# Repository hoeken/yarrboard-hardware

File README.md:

# Yarrboard Hardware

This repo has Kicad symbols, footprints, and models used in the Yarrboard project.

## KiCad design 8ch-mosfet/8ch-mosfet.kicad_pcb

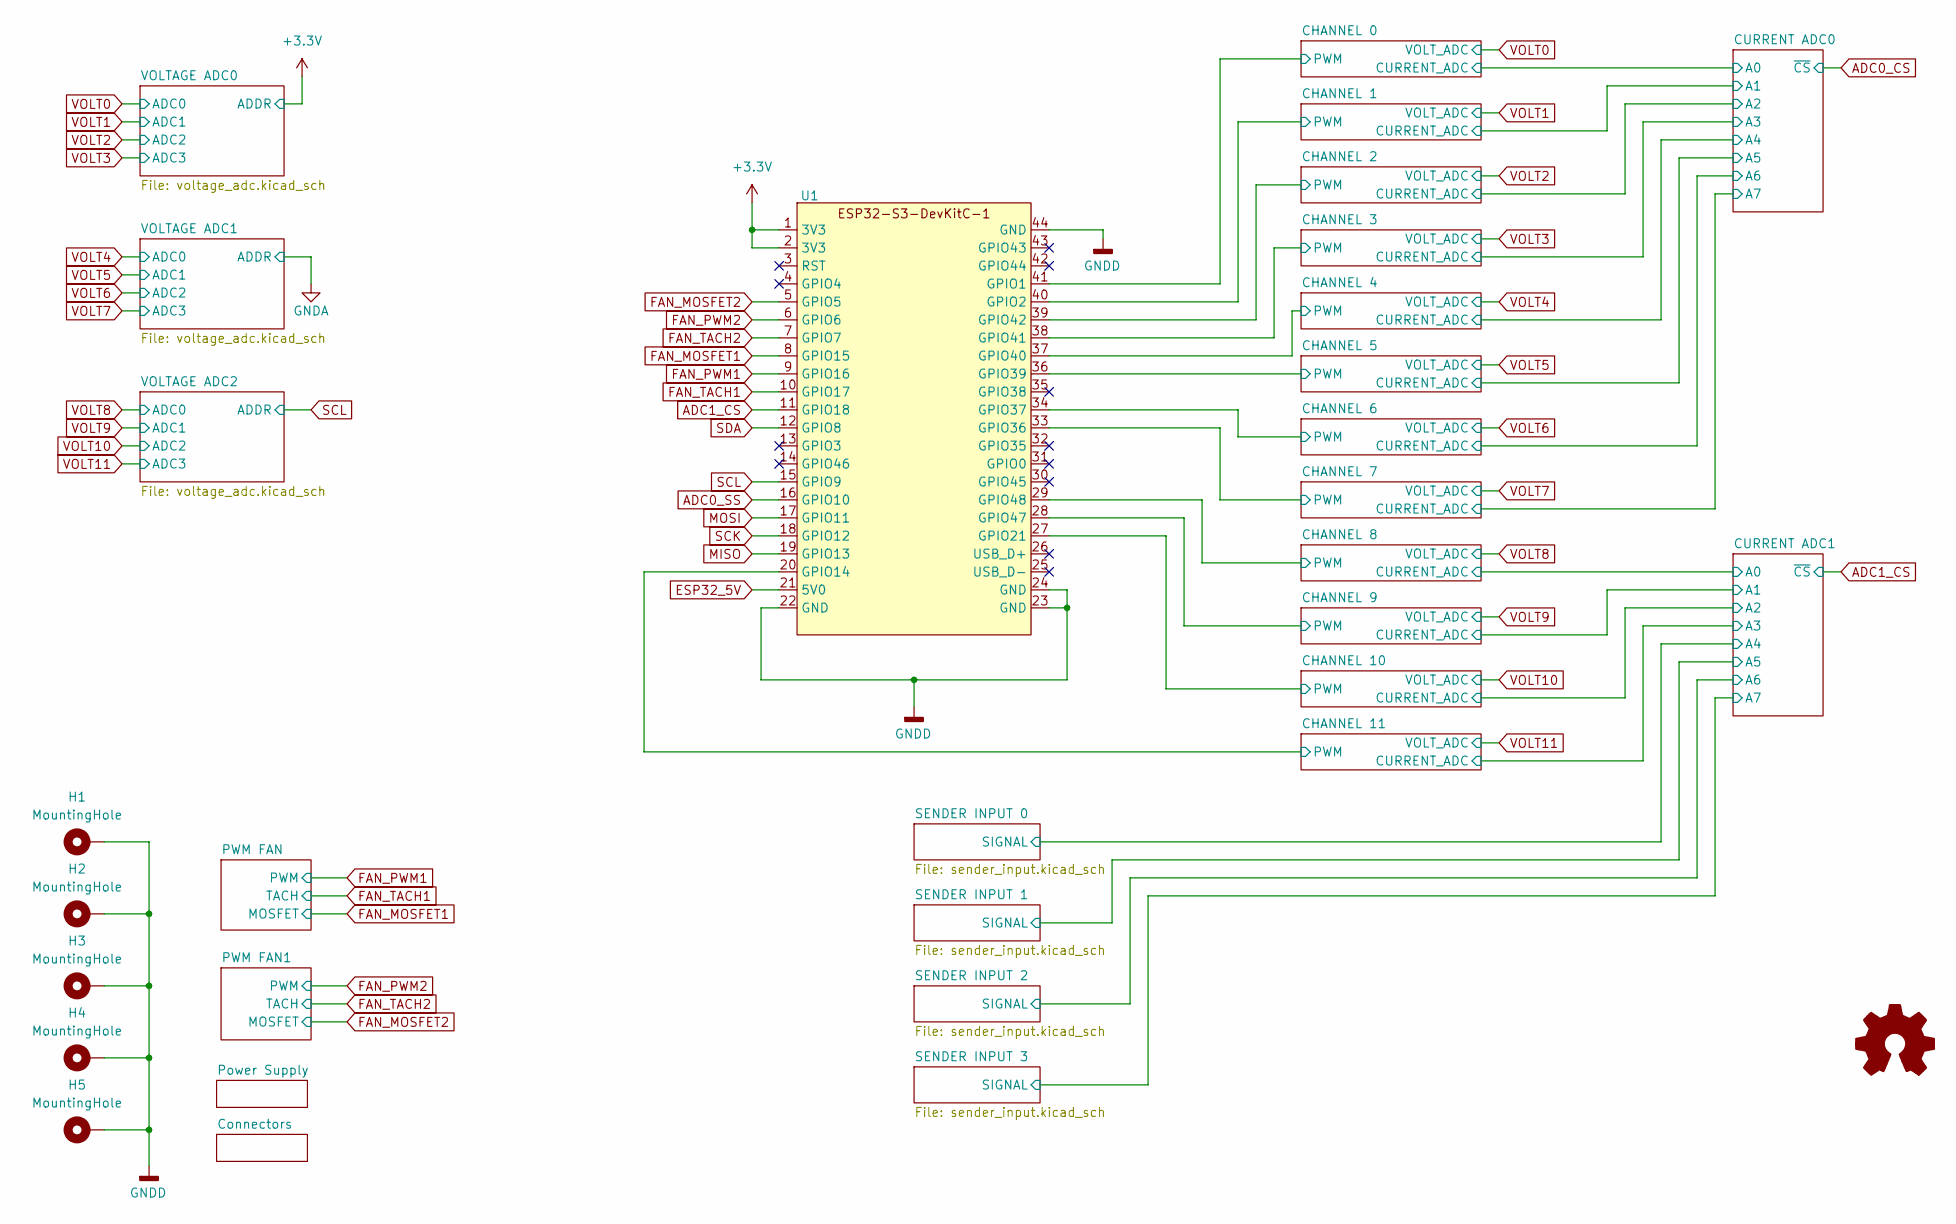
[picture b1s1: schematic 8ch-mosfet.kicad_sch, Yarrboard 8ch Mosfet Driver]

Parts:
H1, H2, H3, H4, H5: MountingHole; MountingHole_3.2mm_M3_DIN965_Pad
U1: Waveshare-ESP32-S3-dev-kit

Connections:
+3.3V: U1.1 (3V3), U1.2 (3V3); also elsewhere on the board
/CHANNEL 0/PWM: U1.41 (GPIO1); also elsewhere on the board
/CHANNEL 1/PWM: U1.40 (GPIO2); also elsewhere on the board
/CHANNEL 2/PWM: U1.39 (GPIO42); also elsewhere on the board
/CHANNEL 3/PWM: U1.38 (GPIO41); also elsewhere on the board
/CHANNEL 4/PWM: U1.37 (GPIO40); also elsewhere on the board
/CHANNEL 5/PWM: U1.36 (GPIO39); also elsewhere on the board
/CHANNEL 6/PWM: U1.34 (GPIO37); also elsewhere on the board
/CHANNEL 7/PWM: U1.33 (GPIO36); also elsewhere on the board
/CHANNEL 8/PWM: U1.29 (GPIO48); also elsewhere on the board
/CHANNEL 9/PWM: U1.28 (GPIO47); also elsewhere on the board
/CHANNEL 10/PWM: U1.27 (GPIO21); also elsewhere on the board
/CHANNEL 11/PWM: U1.20 (GPIO14); also elsewhere on the board
ADC0_SS: U1.16 (GPIO10)
ADC1_CS: U1.11 (GPIO18); also elsewhere on the board
ESP32_5V: U1.21 (5V0); also elsewhere on the board
FAN_MOSFET1: U1.8 (GPIO15); also elsewhere on the board
FAN_MOSFET2: U1.5 (GPIO5); also elsewhere on the board
FAN_PWM1: U1.9 (GPIO16); also elsewhere on the board
FAN_PWM2: U1.6 (GPIO6); also elsewhere on the board
FAN_TACH1: U1.10 (GPIO17); also elsewhere on the board
FAN_TACH2: U1.7 (GPIO7); also elsewhere on the board
GNDD: H1.1, H2.1, H3.1, H4.1, H5.1, U1.22 (GND), U1.23 (GND), U1.24 (GND), U1.44 (GND); also elsewhere on the board
MISO: U1.19 (GPIO13); also elsewhere on the board
MOSI: U1.17 (GPIO11); also elsewhere on the board
SCK: U1.18 (GPIO12); also elsewhere on the board
SCL: U1.15 (GPIO9); also elsewhere on the board
SDA: U1.12 (GPIO8); also elsewhere on the board

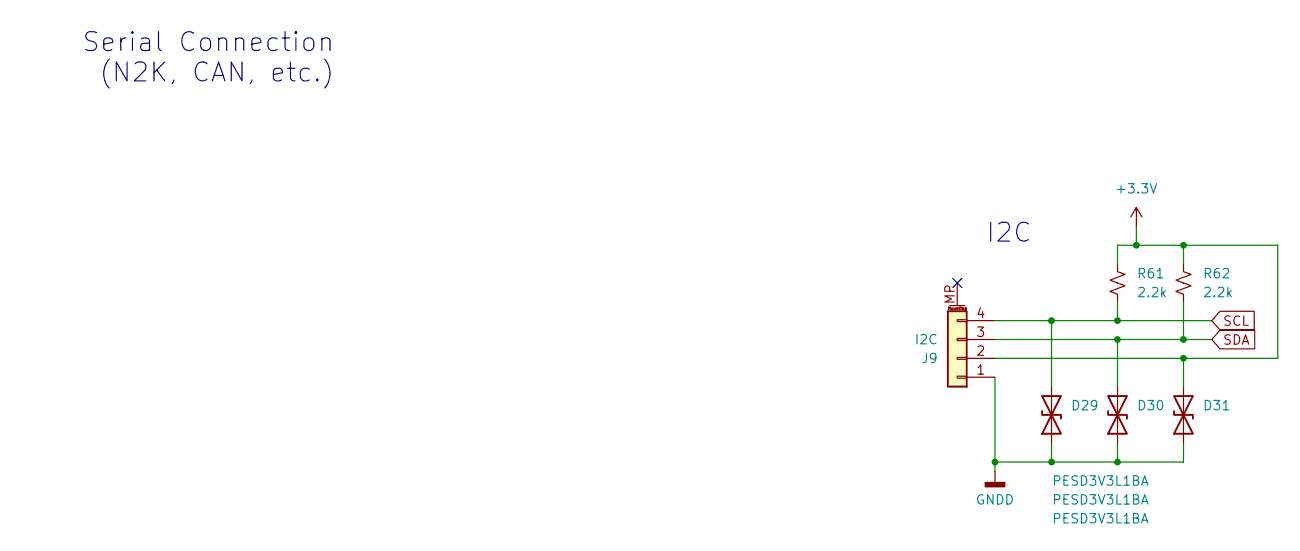
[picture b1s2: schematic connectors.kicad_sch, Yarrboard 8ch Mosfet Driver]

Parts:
D29, D30, D31: PESD3V3L1BA; D_SOD-323_HandSoldering; LCSC C316020
J9: I2C; JST_SH_SM04B-SRSS-TB_1x04-1MP_P1.00mm_Horizontal; LCSC C160404
R61, R62: 2.2k; R_0805_2012Metric_Pad1.20x1.40mm_HandSolder

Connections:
+3.3V: D31.2 (A2), J9.2, R61.2, R62.2; also elsewhere on the board
GNDD: D29.1 (A1), D30.1 (A1), D31.1 (A1), J9.1; also elsewhere on the board
SCL: D29.2 (A2), J9.4, R61.1; also elsewhere on the board
SDA: D30.2 (A2), J9.3, R62.1; also elsewhere on the board

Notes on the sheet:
Serial Connection (N2K, CAN, etc.)
I2C

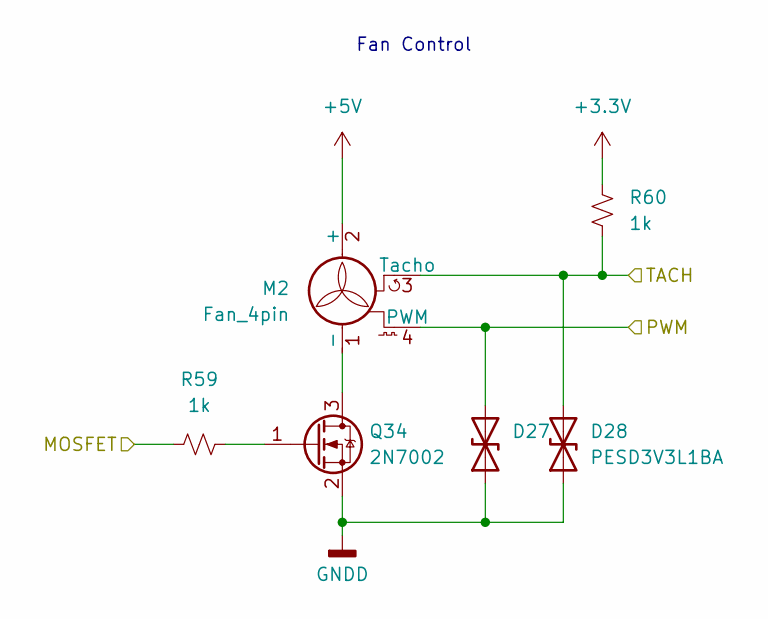
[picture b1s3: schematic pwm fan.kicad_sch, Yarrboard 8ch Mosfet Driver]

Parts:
D27, D28: PESD3V3L1BA; D_SOD-323_HandSoldering; LCSC C316020
M2: Fan_4pin; Molex 0470531000; Mouser 538-47053-1000
Q34: 2N7002; SOT-23
R59, R60: 1k; R_0805_2012Metric_Pad1.20x1.40mm_HandSolder; LCSC C95781

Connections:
+3.3V: R60.2; also elsewhere on the board
+5V: M2.2 (+); also elsewhere on the board
FAN_MOSFET2: R59.2; also elsewhere on the board
FAN_PWM2: D27.2 (A2), M2.4 (PWM); also elsewhere on the board
FAN_TACH2: D28.2 (A2), M2.3 (Tacho), R60.1; also elsewhere on the board
GNDD: D27.1 (A1), D28.1 (A1), Q34.2 (S); also elsewhere on the board
unnamed: M2.1 (-), Q34.3 (D)
unnamed: Q34.1 (G), R59.1

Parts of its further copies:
D25, D26: PESD3V3L1BA; D_SOD-323_HandSoldering; LCSC C316020
M1: Fan_4pin; Molex 0470531000; Mouser 538-47053-1000
Q33: 2N7002; SOT-23
R57, R58: 1k; R_0805_2012Metric_Pad1.20x1.40mm_HandSolder; LCSC C95781

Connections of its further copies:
+3.3V: R58.2; also elsewhere on the board
+5V: M1.2 (+); also elsewhere on the board
FAN_MOSFET1: R57.2; also elsewhere on the board
FAN_PWM1: D25.2 (A2), M1.4 (PWM); also elsewhere on the board
FAN_TACH1: D26.2 (A2), M1.3 (Tacho), R58.1; also elsewhere on the board
GNDD: D25.1 (A1), D26.1 (A1), Q33.2 (S); also elsewhere on the board
unnamed: M1.1 (-), Q33.3 (D)
unnamed: Q33.1 (G), R57.1

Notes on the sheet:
Fan Control

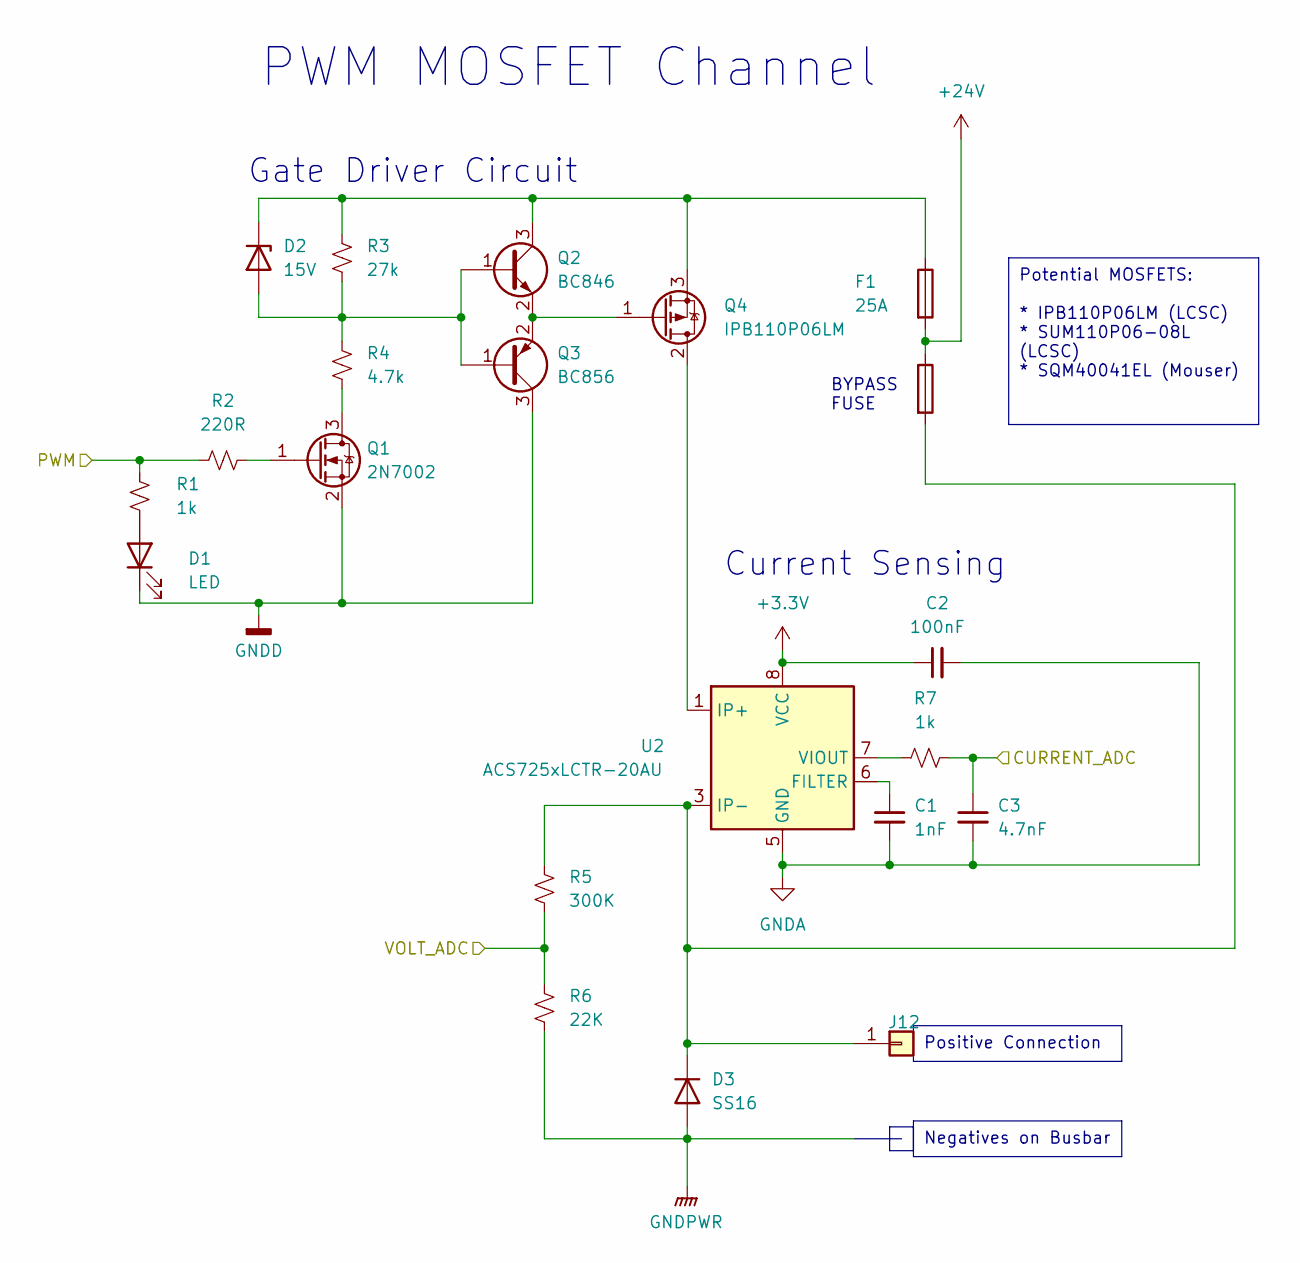
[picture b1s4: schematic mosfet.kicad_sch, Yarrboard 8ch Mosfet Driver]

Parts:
C1: 1nF; C_0805_2012Metric_Pad1.18x1.45mm_HandSolder; Mouser C0805C102J1HACTU
C2: 100nF; C_0805_2012Metric_Pad1.18x1.45mm_HandSolder; Mouser 08053C104KAT4A
C3: 4.7nF; C_0805_2012Metric_Pad1.18x1.45mm_HandSolder; Mouser C0805C472K5RAC
D1: LED; LED_0805_2012Metric_Pad1.15x1.40mm_HandSolder; Mouser 150080RS75000
D2: 15V; D_SOD-323_HandSoldering; Mouser 771-BZX384-C15115
D3: SS16; D_SMA; Mouser 625-SS16-E3
F1: 25A; ATC Bypass Fuse; Mouser 534-3522-3
J12: Conn_01x01; T44001
Q1: 2N7002; SOT-23
Q2: BC846; SOT-23
Q3: BC856; SOT-23
Q4: IPB110P06LM; TO-263-2
R1, R7: 1k; R_0805_2012Metric_Pad1.20x1.40mm_HandSolder; LCSC C95781
R2: 220R; R_0805_2012Metric_Pad1.20x1.40mm_HandSolder; LCSC C114519
R3: 27k; R_0805_2012Metric_Pad1.20x1.40mm_HandSolder
R4: 4.7k; R_0805_2012Metric_Pad1.20x1.40mm_HandSolder
R5: 300K; R_0805_2012Metric_Pad1.20x1.40mm_HandSolder
R6: 22K; R_0805_2012Metric_Pad1.20x1.40mm_HandSolder; LCSC C865312
U2: ACS725xLCTR-20AU; ACS7XX; Mouser 250-725LLCTR20AUT

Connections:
+3.3V: C2.1, U2.8 (VCC); also elsewhere on the board
+24V: F1.2; also elsewhere on the board
/CHANNEL 0/CURRENT_ADC: C3.1, R7.1; also elsewhere on the board
/CHANNEL 0/PWM: R1.2, R2.1; also elsewhere on the board
GNDA: C1.2, C2.2, C3.2, U2.5 (GND); also elsewhere on the board
GNDD: D1.1 (K), Q1.2 (S), Q3.3 (C); also elsewhere on the board
GNDPWR: D3.2 (A), R6.1; also elsewhere on the board
unnamed: D1.2 (A), R1.1
unnamed: D2.2 (A), Q2.1 (B), Q3.1 (B), R3.1, R4.2
unnamed: D2.1 (K), F1.1, Q2.3 (C), Q4.3 (S), R3.2
unnamed: Q1.3 (D), R4.1
unnamed: Q1.1 (G), R2.2
unnamed: Q2.2 (E), Q3.2 (E), Q4.1 (G)
unnamed: Q4.2 (D), U2.1 (IP+), U2.2 (IP+)
unnamed: C1.1, U2.6 (FILTER)
unnamed: R7.2, U2.7 (VIOUT)
VOLT0: R5.1, R6.2; also elsewhere on the board

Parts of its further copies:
C4, C7, C10, C13, C16, C19, C22, C37, C40, C43, C46: 1nF; C_0805_2012Metric_Pad1.18x1.45mm_HandSolder; Mouser C0805C102J1HACTU
C5, C8, C11, C14, C17, C20, C23, C38, C41, C44, C47: 100nF; C_0805_2012Metric_Pad1.18x1.45mm_HandSolder; Mouser 08053C104KAT4A
C6, C9, C12, C15, C18, C21, C24, C39, C42, C45, C48: 4.7nF; C_0805_2012Metric_Pad1.18x1.45mm_HandSolder; Mouser C0805C472K5RAC
D4, D7, D10, D13, D16, D19, D22, D37, D40, D43, D46: LED; LED_0805_2012Metric_Pad1.15x1.40mm_HandSolder; Mouser 150080RS75000
D5, D8, D11, D14, D17, D20, D23, D38, D41, D44, D47: 15V; D_SOD-323_HandSoldering; Mouser 771-BZX384-C15115
D6, D9, D12, D15, D18, D21, D24, D39, D42, D45, D48: SS16; D_SMA; Mouser 625-SS16-E3
F2, F3, F4, F5, F6, F7, F8, F11, F12, F13, F14: 25A; ATC Bypass Fuse; Mouser 534-3522-3
J1, J2, J3, J4, J5, J6, J7, J8, J13, J14, J15: Conn_01x01; T44001
Q5, Q9, Q13, Q17, Q21, Q25, Q29, Q35, Q39, Q43, Q47: 2N7002; SOT-23
Q6, Q10, Q14, Q18, Q22, Q26, Q30, Q36, Q40, Q44, Q48: BC846; SOT-23
Q7, Q11, Q15, Q19, Q23, Q27, Q31, Q37, Q41, Q45, Q49: BC856; SOT-23
Q8, Q12, Q16, Q20, Q24, Q28, Q32, Q38, Q42, Q46, Q50: IPB110P06LM; TO-263-2
R8, R14, R15, R21, R22, R28, R29, R35, R36, R42, R43, R49, R50, R56, R69, R75, R76, R82, R83, R89, R90, R96: 1k; R_0805_2012Metric_Pad1.20x1.40mm_HandSolder; LCSC C95781
R9, R16, R23, R30, R37, R44, R51, R70, R77, R84, R91: 220R; R_0805_2012Metric_Pad1.20x1.40mm_HandSolder; LCSC C114519
R10, R17, R24, R31, R38, R45, R52, R71, R78, R85, R92: 27k; R_0805_2012Metric_Pad1.20x1.40mm_HandSolder
R11, R18, R25, R32, R39, R46, R53, R72, R79, R86, R93: 4.7k; R_0805_2012Metric_Pad1.20x1.40mm_HandSolder
R12, R19, R26, R33, R40, R47, R54, R73, R80, R87, R94: 300K; R_0805_2012Metric_Pad1.20x1.40mm_HandSolder
R13, R20, R27, R34, R41, R48, R55, R74, R81, R88, R95: 22K; R_0805_2012Metric_Pad1.20x1.40mm_HandSolder; LCSC C865312
U3, U4, U5, U6, U7, U8, U9, U15, U16, U17, U18: ACS725xLCTR-20AU; ACS7XX; Mouser 250-725LLCTR20AUT

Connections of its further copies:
+3.3V: C5.1, C8.1, C11.1, C14.1, C17.1, C20.1, C23.1, C38.1, C41.1, C44.1, C47.1, U3.8 (VCC), U4.8 (VCC), U5.8 (VCC), U6.8 (VCC), U7.8 (VCC), U8.8 (VCC), U9.8 (VCC), U15.8 (VCC), U16.8 (VCC), U17.8 (VCC), U18.8 (VCC); also elsewhere on the board
+24V: F2.2, F3.2, F4.2, F5.2, F6.2, F7.2, F8.2, F11.2, F12.2, F13.2, F14.2; also elsewhere on the board
/CHANNEL 1/CURRENT_ADC: C6.1, R14.1; also elsewhere on the board
/CHANNEL 1/PWM: R8.2, R9.1; also elsewhere on the board
/CHANNEL 2/CURRENT_ADC: C9.1, R21.1; also elsewhere on the board
/CHANNEL 2/PWM: R15.2, R16.1; also elsewhere on the board
/CHANNEL 3/CURRENT_ADC: C12.1, R28.1; also elsewhere on the board
/CHANNEL 3/PWM: R22.2, R23.1; also elsewhere on the board
/CHANNEL 4/CURRENT_ADC: C15.1, R35.1; also elsewhere on the board
/CHANNEL 4/PWM: R29.2, R30.1; also elsewhere on the board
/CHANNEL 5/CURRENT_ADC: C18.1, R42.1; also elsewhere on the board
/CHANNEL 5/PWM: R36.2, R37.1; also elsewhere on the board
/CHANNEL 6/CURRENT_ADC: C21.1, R49.1; also elsewhere on the board
/CHANNEL 6/PWM: R43.2, R44.1; also elsewhere on the board
/CHANNEL 7/CURRENT_ADC: C24.1, R56.1; also elsewhere on the board
/CHANNEL 7/PWM: R50.2, R51.1; also elsewhere on the board
/CHANNEL 8/CURRENT_ADC: C39.1, R75.1; also elsewhere on the board
/CHANNEL 8/PWM: R69.2, R70.1; also elsewhere on the board
/CHANNEL 9/CURRENT_ADC: C42.1, R82.1; also elsewhere on the board
/CHANNEL 9/PWM: R76.2, R77.1; also elsewhere on the board
/CHANNEL 10/CURRENT_ADC: C45.1, R89.1; also elsewhere on the board
/CHANNEL 10/PWM: R83.2, R84.1; also elsewhere on the board
/CHANNEL 11/CURRENT_ADC: C48.1, R96.1; also elsewhere on the board
/CHANNEL 11/PWM: R90.2, R91.1; also elsewhere on the board
GNDA: C4.2, C5.2, C6.2, C7.2, C8.2, C9.2, C10.2, C11.2, C12.2, C13.2, C14.2, C15.2, C16.2, C17.2, C18.2, C19.2, C20.2, C21.2, C22.2, C23.2, C24.2, C37.2, C38.2, C39.2, C40.2, C41.2, C42.2, C43.2, C44.2, C45.2, C46.2, C47.2, C48.2, U3.5 (GND), U4.5 (GND), U5.5 (GND), U6.5 (GND), U7.5 (GND), U8.5 (GND), U9.5 (GND), U15.5 (GND), U16.5 (GND), U17.5 (GND), U18.5 (GND); also elsewhere on the board
GNDD: D4.1 (K), D7.1 (K), D10.1 (K), D13.1 (K), D16.1 (K), D19.1 (K), D22.1 (K), D37.1 (K), D40.1 (K), D43.1 (K), D46.1 (K), Q5.2 (S), Q7.3 (C), Q9.2 (S), Q11.3 (C), Q13.2 (S), Q15.3 (C), Q17.2 (S), Q19.3 (C), Q21.2 (S), Q23.3 (C), Q25.2 (S), Q27.3 (C), Q29.2 (S), Q31.3 (C), Q35.2 (S), Q37.3 (C), Q39.2 (S), Q41.3 (C), Q43.2 (S), Q45.3 (C), Q47.2 (S), Q49.3 (C); also elsewhere on the board
GNDPWR: D6.2 (A), D9.2 (A), D12.2 (A), D15.2 (A), D18.2 (A), D21.2 (A), D24.2 (A), D39.2 (A), D42.2 (A), D45.2 (A), D48.2 (A), R13.1, R20.1, R27.1, R34.1, R41.1, R48.1, R55.1, R74.1, R81.1, R88.1, R95.1; also elsewhere on the board
unnamed: D4.2 (A), R8.1
unnamed: D5.2 (A), Q6.1 (B), Q7.1 (B), R10.1, R11.2
unnamed: D5.1 (K), F2.1, Q6.3 (C), Q8.3 (S), R10.2
unnamed: D6.1 (K), F2.3, J2.1, R12.2, U3.3 (IP-), U3.4 (IP-)
unnamed: D7.2 (A), R15.1
unnamed: D8.2 (A), Q10.1 (B), Q11.1 (B), R17.1, R18.2
unnamed: D8.1 (K), F3.1, Q10.3 (C), Q12.3 (S), R17.2
unnamed: D9.1 (K), F3.3, J3.1, R19.2, U4.3 (IP-), U4.4 (IP-)
unnamed: D10.2 (A), R22.1
unnamed: D11.2 (A), Q14.1 (B), Q15.1 (B), R24.1, R25.2
unnamed: D11.1 (K), F4.1, Q14.3 (C), Q16.3 (S), R24.2
unnamed: D12.1 (K), F4.3, J4.1, R26.2, U5.3 (IP-), U5.4 (IP-)
unnamed: D13.2 (A), R29.1
unnamed: D14.2 (A), Q18.1 (B), Q19.1 (B), R31.1, R32.2
unnamed: D14.1 (K), F5.1, Q18.3 (C), Q20.3 (S), R31.2
unnamed: D15.1 (K), F5.3, J5.1, R33.2, U6.3 (IP-), U6.4 (IP-)
unnamed: D16.2 (A), R36.1
unnamed: D17.2 (A), Q22.1 (B), Q23.1 (B), R38.1, R39.2
unnamed: D17.1 (K), F6.1, Q22.3 (C), Q24.3 (S), R38.2
unnamed: D18.1 (K), F6.3, J6.1, R40.2, U7.3 (IP-), U7.4 (IP-)
unnamed: D19.2 (A), R43.1
unnamed: D20.2 (A), Q26.1 (B), Q27.1 (B), R45.1, R46.2
unnamed: D20.1 (K), F7.1, Q26.3 (C), Q28.3 (S), R45.2
unnamed: D21.1 (K), F7.3, J7.1, R47.2, U8.3 (IP-), U8.4 (IP-)
unnamed: D22.2 (A), R50.1
unnamed: D23.2 (A), Q30.1 (B), Q31.1 (B), R52.1, R53.2
unnamed: D23.1 (K), F8.1, Q30.3 (C), Q32.3 (S), R52.2
unnamed: D24.1 (K), F8.3, J8.1, R54.2, U9.3 (IP-), U9.4 (IP-)
unnamed: D37.2 (A), R69.1
unnamed: D38.2 (A), Q36.1 (B), Q37.1 (B), R71.1, R72.2
unnamed: D38.1 (K), F11.1, Q36.3 (C), Q38.3 (S), R71.2
unnamed: D40.2 (A), R76.1
unnamed: D41.2 (A), Q40.1 (B), Q41.1 (B), R78.1, R79.2
unnamed: D41.1 (K), F12.1, Q40.3 (C), Q42.3 (S), R78.2
unnamed: D42.1 (K), F12.3, J13.1, R80.2, U16.3 (IP-), U16.4 (IP-)
unnamed: D43.2 (A), R83.1
unnamed: D44.2 (A), Q44.1 (B), Q45.1 (B), R85.1, R86.2
unnamed: D44.1 (K), F13.1, Q44.3 (C), Q46.3 (S), R85.2
unnamed: D45.1 (K), F13.3, J14.1, R87.2, U17.3 (IP-), U17.4 (IP-)
unnamed: D46.2 (A), R90.1
unnamed: D47.2 (A), Q48.1 (B), Q49.1 (B), R92.1, R93.2
unnamed: D47.1 (K), F14.1, Q48.3 (C), Q50.3 (S), R92.2
unnamed: D48.1 (K), F14.3, J15.1, R94.2, U18.3 (IP-), U18.4 (IP-)
unnamed: Q5.3 (D), R11.1
unnamed: Q5.1 (G), R9.2
unnamed: Q6.2 (E), Q7.2 (E), Q8.1 (G)
unnamed: Q8.2 (D), U3.1 (IP+), U3.2 (IP+)
unnamed: Q9.3 (D), R18.1
unnamed: Q9.1 (G), R16.2
unnamed: Q10.2 (E), Q11.2 (E), Q12.1 (G)
unnamed: Q12.2 (D), U4.1 (IP+), U4.2 (IP+)
unnamed: Q13.3 (D), R25.1
unnamed: Q13.1 (G), R23.2
unnamed: Q14.2 (E), Q15.2 (E), Q16.1 (G)
unnamed: Q16.2 (D), U5.1 (IP+), U5.2 (IP+)
unnamed: Q17.3 (D), R32.1
unnamed: Q17.1 (G), R30.2
unnamed: Q18.2 (E), Q19.2 (E), Q20.1 (G)
unnamed: Q20.2 (D), U6.1 (IP+), U6.2 (IP+)
unnamed: Q21.3 (D), R39.1
unnamed: Q21.1 (G), R37.2
unnamed: Q22.2 (E), Q23.2 (E), Q24.1 (G)
unnamed: Q24.2 (D), U7.1 (IP+), U7.2 (IP+)
unnamed: Q25.3 (D), R46.1
unnamed: Q25.1 (G), R44.2
unnamed: Q26.2 (E), Q27.2 (E), Q28.1 (G)
unnamed: Q28.2 (D), U8.1 (IP+), U8.2 (IP+)
unnamed: Q29.3 (D), R53.1
unnamed: Q29.1 (G), R51.2
unnamed: Q30.2 (E), Q31.2 (E), Q32.1 (G)
unnamed: Q32.2 (D), U9.1 (IP+), U9.2 (IP+)
unnamed: Q35.3 (D), R72.1
unnamed: Q35.1 (G), R70.2
unnamed: Q36.2 (E), Q37.2 (E), Q38.1 (G)
unnamed: Q38.2 (D), U15.1 (IP+), U15.2 (IP+)
unnamed: Q39.3 (D), R79.1
unnamed: Q39.1 (G), R77.2
unnamed: Q40.2 (E), Q41.2 (E), Q42.1 (G)
unnamed: Q42.2 (D), U16.1 (IP+), U16.2 (IP+)
unnamed: Q43.3 (D), R86.1
unnamed: Q43.1 (G), R84.2
unnamed: Q44.2 (E), Q45.2 (E), Q46.1 (G)
unnamed: Q46.2 (D), U17.1 (IP+), U17.2 (IP+)
unnamed: Q47.3 (D), R93.1
unnamed: Q47.1 (G), R91.2
unnamed: Q48.2 (E), Q49.2 (E), Q50.1 (G)
unnamed: Q50.2 (D), U18.1 (IP+), U18.2 (IP+)
unnamed: C4.1, U3.6 (FILTER)
unnamed: R14.2, U3.7 (VIOUT)
unnamed: C7.1, U4.6 (FILTER)
unnamed: R21.2, U4.7 (VIOUT)
unnamed: C10.1, U5.6 (FILTER)
unnamed: R28.2, U5.7 (VIOUT)
unnamed: C13.1, U6.6 (FILTER)
unnamed: R35.2, U6.7 (VIOUT)
unnamed: C16.1, U7.6 (FILTER)
unnamed: R42.2, U7.7 (VIOUT)
unnamed: C19.1, U8.6 (FILTER)
unnamed: R49.2, U8.7 (VIOUT)
unnamed: C22.1, U9.6 (FILTER)
unnamed: R56.2, U9.7 (VIOUT)
unnamed: C37.1, U15.6 (FILTER)
unnamed: R75.2, U15.7 (VIOUT)
unnamed: C40.1, U16.6 (FILTER)
unnamed: R82.2, U16.7 (VIOUT)
unnamed: C43.1, U17.6 (FILTER)
unnamed: R89.2, U17.7 (VIOUT)
unnamed: C46.1, U18.6 (FILTER)
unnamed: R96.2, U18.7 (VIOUT)
VOLT1: R12.1, R13.2; also elsewhere on the board
VOLT2: R19.1, R20.2; also elsewhere on the board
VOLT3: R26.1, R27.2; also elsewhere on the board
VOLT4: R33.1, R34.2; also elsewhere on the board
VOLT5: R40.1, R41.2; also elsewhere on the board
VOLT6: R47.1, R48.2; also elsewhere on the board
VOLT7: R54.1, R55.2; also elsewhere on the board
VOLT8: R73.1, R74.2; also elsewhere on the board
VOLT9: R80.1, R81.2; also elsewhere on the board
VOLT10: R87.1, R88.2; also elsewhere on the board
VOLT11: R94.1, R95.2; also elsewhere on the board

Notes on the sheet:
Negatives on Busbar
Positive Connection
Potential MOSFETS: * IPB110P06LM (LCSC) * SUM110P06-08L (LCSC) * SQM40041EL (Mouser)
Current Sensing
PWM MOSFET Channel
BYPASS FUSE
Gate Driver Circuit

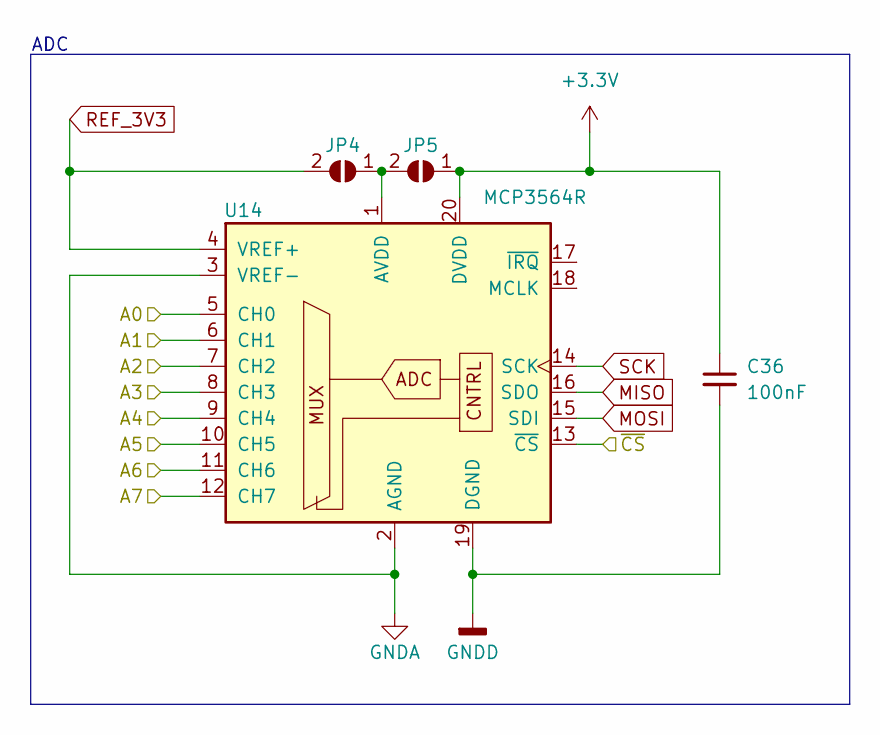
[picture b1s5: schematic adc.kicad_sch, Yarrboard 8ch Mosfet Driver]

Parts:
C36: 100nF; C_0805_2012Metric_Pad1.18x1.45mm_HandSolder; Mouser 08053C104KAT4A
JP4, JP5: SolderJumper_2_Open; SolderJumper-2_P1.3mm_Open_RoundedPad1.0x1.5mm
U14: MCP3564R; TSSOP-20_4.4x6.5mm_P0.65mm

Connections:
+3.3V: C36.1, JP5.1 (A), U14.20 (DVDD); also elsewhere on the board
/CHANNEL 8/CURRENT_ADC: U14.5 (CH0); also elsewhere on the board
/CHANNEL 9/CURRENT_ADC: U14.6 (CH1); also elsewhere on the board
/CHANNEL 10/CURRENT_ADC: U14.7 (CH2); also elsewhere on the board
/CHANNEL 11/CURRENT_ADC: U14.8 (CH3); also elsewhere on the board
/CURRENT ADC1/A6: U14.11 (CH6); also elsewhere on the board
/CURRENT ADC1/A7: U14.12 (CH7); also elsewhere on the board
ADC1_CS: U14.13 (~CS); also elsewhere on the board
GNDA: U14.2 (AGND), U14.3 (VREF-); also elsewhere on the board
GNDD: C36.2, U14.19 (DGND); also elsewhere on the board
MISO: U14.16 (SDO); also elsewhere on the board
MOSI: U14.15 (SDI); also elsewhere on the board
unnamed: JP4.1 (A), JP5.2 (B), U14.1 (AVDD)
REF_3V3: JP4.2 (B), U14.4 (VREF+); also elsewhere on the board
SCK: U14.14 (SCK); also elsewhere on the board

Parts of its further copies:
C25: 100nF; C_0805_2012Metric_Pad1.18x1.45mm_HandSolder; Mouser 08053C104KAT4A
JP1, JP2: SolderJumper_2_Open; SolderJumper-2_P1.3mm_Open_RoundedPad1.0x1.5mm
U10: MCP3564R; TSSOP-20_4.4x6.5mm_P0.65mm

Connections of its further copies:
+3.3V: C25.1, JP2.1 (A), U10.20 (DVDD); also elsewhere on the board
/CHANNEL 0/CURRENT_ADC: U10.5 (CH0); also elsewhere on the board
/CHANNEL 1/CURRENT_ADC: U10.6 (CH1); also elsewhere on the board
/CHANNEL 2/CURRENT_ADC: U10.7 (CH2); also elsewhere on the board
/CHANNEL 3/CURRENT_ADC: U10.8 (CH3); also elsewhere on the board
/CHANNEL 4/CURRENT_ADC: U10.9 (CH4); also elsewhere on the board
/CHANNEL 5/CURRENT_ADC: U10.10 (CH5); also elsewhere on the board
/CHANNEL 6/CURRENT_ADC: U10.11 (CH6); also elsewhere on the board
/CHANNEL 7/CURRENT_ADC: U10.12 (CH7); also elsewhere on the board
ADC0_CS: U10.13 (~CS)
GNDA: U10.2 (AGND), U10.3 (VREF-); also elsewhere on the board
GNDD: C25.2, U10.19 (DGND); also elsewhere on the board
MISO: U10.16 (SDO); also elsewhere on the board
MOSI: U10.15 (SDI); also elsewhere on the board
unnamed: JP1.1 (A), JP2.2 (B), U10.1 (AVDD)
REF_3V3: JP1.2 (B), U10.4 (VREF+); also elsewhere on the board
SCK: U10.14 (SCK); also elsewhere on the board

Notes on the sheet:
ADC

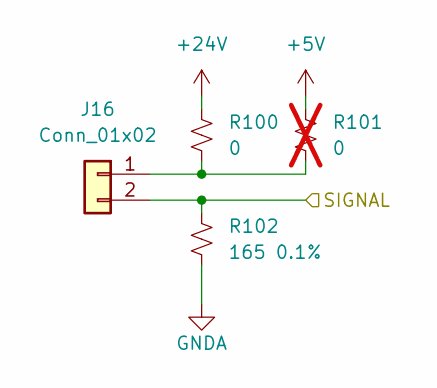
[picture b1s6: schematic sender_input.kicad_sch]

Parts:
J16: Conn_01x02; JST_PH_B2B-PH-K_1x02_P2.00mm_Vertical
R100: 0; R_0805_2012Metric_Pad1.20x1.40mm_HandSolder
R101: 0; R_0805_2012Metric_Pad1.20x1.40mm_HandSolder; not fitted
R102: 165 0.1%; R_0805_2012Metric_Pad1.20x1.40mm_HandSolder

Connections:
+5V: R101.2; also elsewhere on the board
+24V: R100.2; also elsewhere on the board
GNDA: R102.1; also elsewhere on the board

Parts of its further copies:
J17, J18, J19: Conn_01x02; JST_PH_B2B-PH-K_1x02_P2.00mm_Vertical
R97, R103, R106: 0; R_0805_2012Metric_Pad1.20x1.40mm_HandSolder
R98, R104, R107: 0; R_0805_2012Metric_Pad1.20x1.40mm_HandSolder; not fitted
R99, R105, R108: 165 0.1%; R_0805_2012Metric_Pad1.20x1.40mm_HandSolder

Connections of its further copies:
+5V: R98.2, R104.2, R107.2; also elsewhere on the board
+24V: R97.2, R103.2, R106.2; also elsewhere on the board
/CURRENT ADC1/A6: J18.2, R105.2; also elsewhere on the board
/CURRENT ADC1/A7: J19.2, R108.2; also elsewhere on the board
GNDA: R99.1, R105.1, R108.1; also elsewhere on the board
unnamed: J18.1, R103.1, R104.1
unnamed: J19.1, R106.1, R107.1

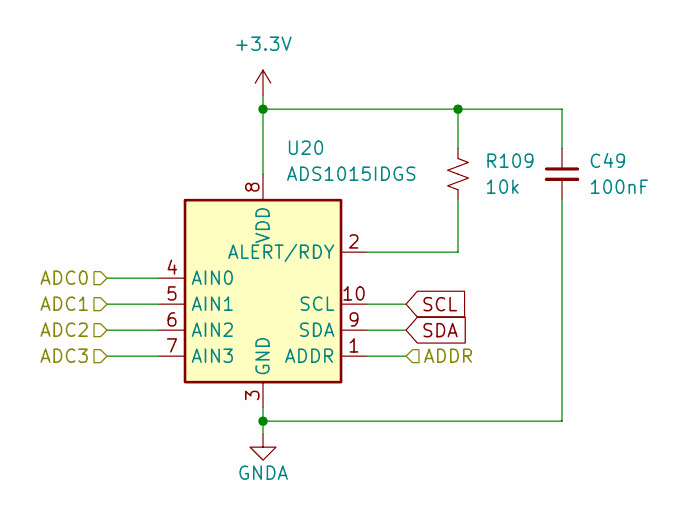
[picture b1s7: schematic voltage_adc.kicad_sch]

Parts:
C49: 100nF; C_0805_2012Metric_Pad1.18x1.45mm_HandSolder; Mouser 08053C104KAT4A
R109: 10k; R_0805_2012Metric_Pad1.20x1.40mm_HandSolder
U20: ADS1015IDGS; TSSOP-10_3x3mm_P0.5mm

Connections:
+3.3V: C49.1, R109.2, U20.8 (VDD); also elsewhere on the board
GNDA: C49.2, U20.1 (ADDR), U20.3 (GND); also elsewhere on the board
SCL: U20.10 (SCL); also elsewhere on the board
SDA: U20.9 (SDA); also elsewhere on the board
VOLT4: U20.4 (AIN0); also elsewhere on the board
VOLT5: U20.5 (AIN1); also elsewhere on the board
VOLT6: U20.6 (AIN2); also elsewhere on the board
VOLT7: U20.7 (AIN3); also elsewhere on the board

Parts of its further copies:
C50, C51: 100nF; C_0805_2012Metric_Pad1.18x1.45mm_HandSolder; Mouser 08053C104KAT4A
R110, R111: 10k; R_0805_2012Metric_Pad1.20x1.40mm_HandSolder
U19, U21: ADS1015IDGS; TSSOP-10_3x3mm_P0.5mm

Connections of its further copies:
+3.3V: C50.1, C51.1, R110.2, R111.2, U19.1 (ADDR), U19.8 (VDD), U21.8 (VDD); also elsewhere on the board
GNDA: C50.2, C51.2, U19.3 (GND), U21.3 (GND); also elsewhere on the board
unnamed: R111.1, U21.2 (ALERT/RDY)
SCL: U19.10 (SCL), U21.1 (ADDR), U21.10 (SCL); also elsewhere on the board
SDA: U19.9 (SDA), U21.9 (SDA); also elsewhere on the board
VOLT0: U19.4 (AIN0); also elsewhere on the board
VOLT1: U19.5 (AIN1); also elsewhere on the board
VOLT2: U19.6 (AIN2); also elsewhere on the board
VOLT3: U19.7 (AIN3); also elsewhere on the board
VOLT8: U21.4 (AIN0); also elsewhere on the board
VOLT9: U21.5 (AIN1); also elsewhere on the board
VOLT10: U21.6 (AIN2); also elsewhere on the board
VOLT11: U21.7 (AIN3); also elsewhere on the board

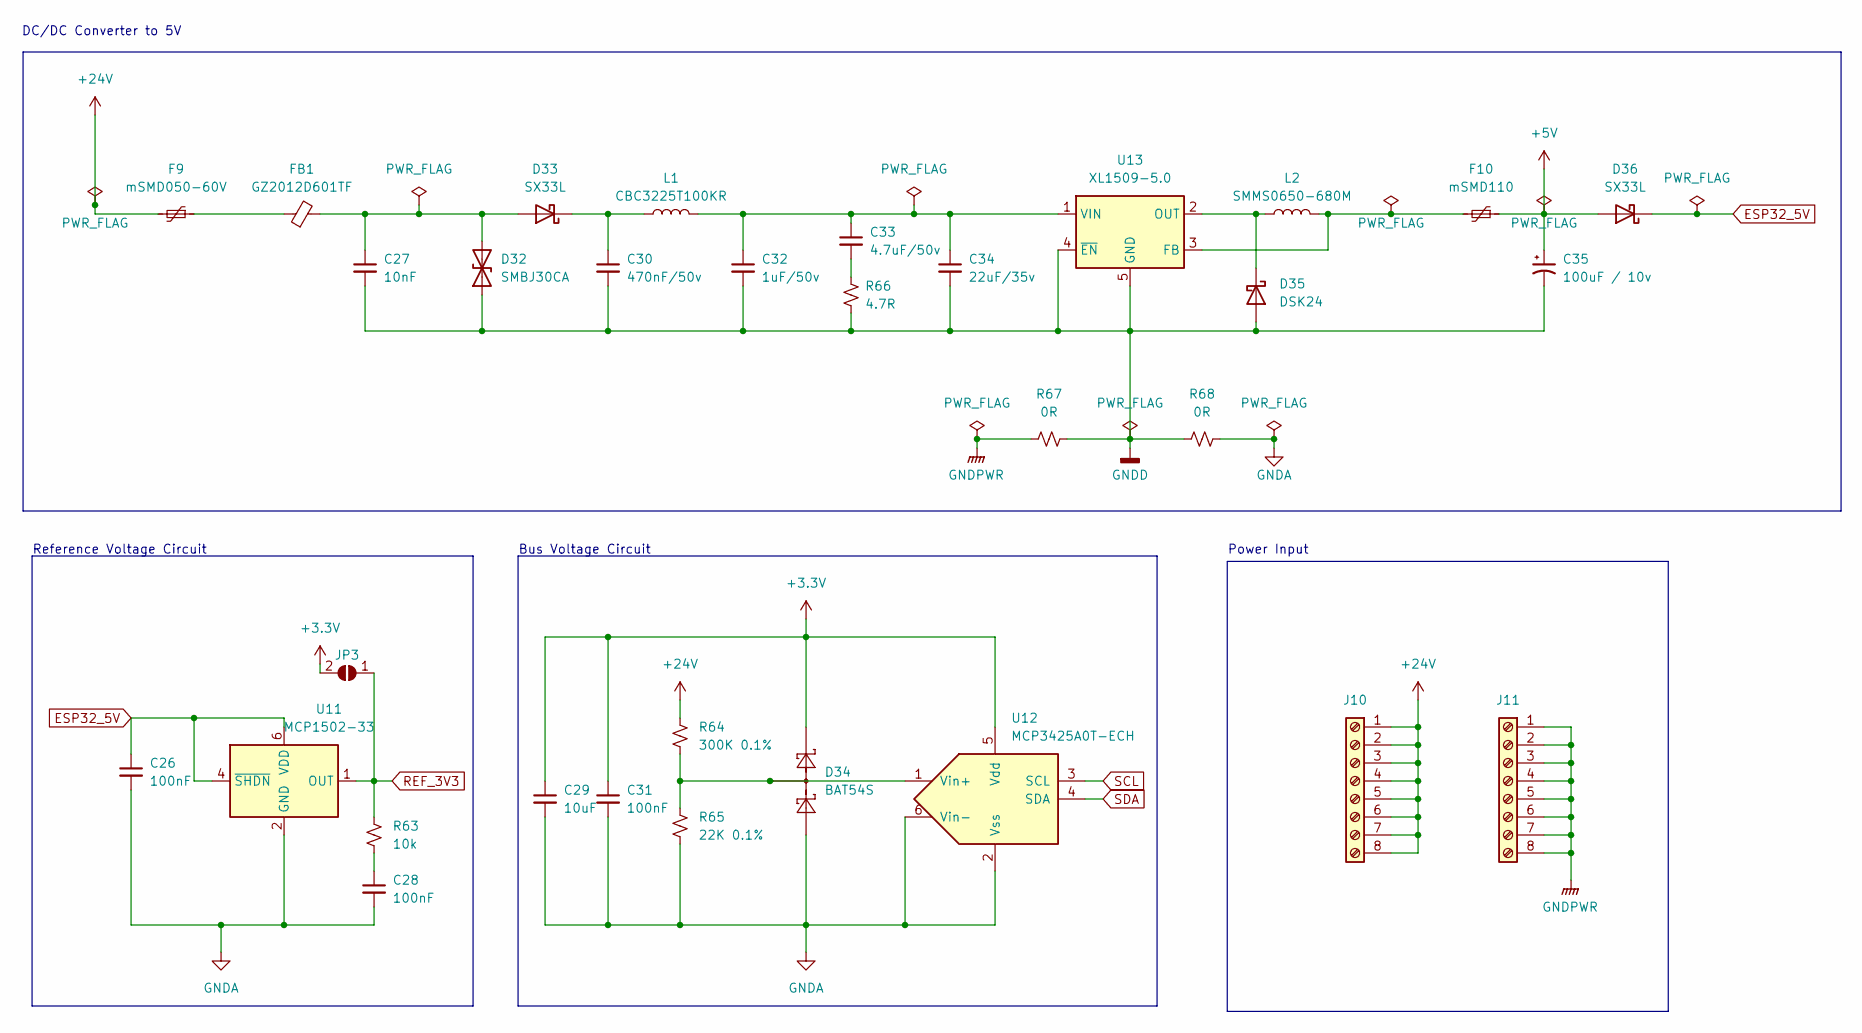
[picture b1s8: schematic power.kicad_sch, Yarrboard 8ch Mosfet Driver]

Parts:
C26, C28, C31: 100nF; C_0805_2012Metric_Pad1.18x1.45mm_HandSolder; Mouser 08053C104KAT4A
C27: 10nF; C_0805_2012Metric_Pad1.18x1.45mm_HandSolder
C29: 10uF; C_0805_2012Metric_Pad1.18x1.45mm_HandSolder
C30: 470nF/50v; C_0805_2012Metric_Pad1.18x1.45mm_HandSolder
C32: 1uF/50v; C_0805_2012Metric_Pad1.18x1.45mm_HandSolder
C33: 4.7uF/50v; C_0805_2012Metric_Pad1.18x1.45mm_HandSolder
C34: 22uF/35v; C_0805_2012Metric_Pad1.18x1.45mm_HandSolder
C35: 100uF / 10v; CP_EIA-3528-21_Kemet-B; LCSC C90975
D32: SMBJ30CA; D_SMB; LCSC C284101
D33, D36: SX33L; D_SMA; Mouser 241-SX33L_R1_00001
D34: BAT54S; SOT-23; LCSC C727126
D35: DSK24; D_SOD-123; Mouser 610-CMHSH5-2L
F9: mSMD050-60V; Fuse_1812_4532Metric_Pad1.30x3.40mm_HandSolder; LCSC C70113
F10: mSMD110; Fuse_1812_4532Metric_Pad1.30x3.40mm_HandSolder; LCSC C69691
FB1: GZ2012D601TF; L_0805_2012Metric; LCSC C1017
J10, J11: Screw_Terminal_01x08; Busbar Rev D
JP3: SolderJumper_2_Open; SolderJumper-2_P1.3mm_Open_RoundedPad1.0x1.5mm
L1: CBC3225T100KR; L_1210_3225Metric; LCSC C90321
L2: SMMS0650-680M; L_Chilisin_BMRB00060650; LCSC C2894721
R63: 10k; R_0805_2012Metric_Pad1.20x1.40mm_HandSolder
R64: 300K 0.1%; R_0805_2012Metric_Pad1.20x1.40mm_HandSolder; LCSC C865386
R65: 22K 0.1%; R_0805_2012Metric_Pad1.20x1.40mm_HandSolder; LCSC C865312
R66: 4.7R; R_0805_2012Metric_Pad1.20x1.40mm_HandSolder
R67, R68: 0R; R_0805_2012Metric_Pad1.20x1.40mm_HandSolder
U11: MCP1502-33; SOT-23-6; Mouser 579-MCP1502T-33E/CHY
U12: MCP3425A0T-ECH; SOT-23-6; Mouser 579-MCP3425A0T-E/CH
U13: XL1509-5.0; SOIC-8_3.9x4.9mm_P1.27mm; LCSC C2902368

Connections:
+3.3V: C29.1, C31.1, D34.2 (K), JP3.2 (B), U12.5 (Vdd); also elsewhere on the board
+5V: C35.1, D36.2 (A), F10.1; also elsewhere on the board
+24V: F9.2, J10.1, J10.2, J10.3, J10.4, J10.5, J10.6, J10.7, J10.8, R64.2; also elsewhere on the board
ESP32_5V: C26.1, D36.1 (K), U11.4 (~SHDN), U11.6 (VDD); also elsewhere on the board
GNDA: C26.2, C28.2, C29.2, C31.2, D34.1 (A), R65.1, R68.1, U11.2 (GND), U11.3 (GND), U11.5 (GND), U12.2 (Vss), U12.6 (Vin-); also elsewhere on the board
GNDD: C27.2, C30.2, C32.2, C34.2, C35.2, D32.1 (A1), D35.2 (A), R66.2, R67.1, R68.2, U13.4 (~EN), U13.5 (GND), U13.6 (GND), U13.7 (GND), U13.8 (GND); also elsewhere on the board
GNDPWR: J11.1, J11.2, J11.3, J11.4, J11.5, J11.6, J11.7, J11.8, R67.2; also elsewhere on the board
unnamed: C28.1, R63.1
unnamed: C33.2, R66.1
unnamed: C27.1, D32.2 (A2), D33.2 (A), FB1.2
unnamed: C30.1, D33.1 (K), L1.1
unnamed: D34.3 (COM), R64.1, R65.2, U12.1 (Vin+)
unnamed: D35.1 (K), L2.1, U13.2 (OUT)
unnamed: F9.1, FB1.1
unnamed: F10.2, L2.2, U13.3 (FB)
unnamed: C32.1, C33.1, C34.1, L1.2, U13.1 (VIN)
REF_3V3: JP3.1 (A), R63.2, U11.1 (OUT); also elsewhere on the board
SCL: U12.3 (SCL); also elsewhere on the board
SDA: U12.4 (SDA); also elsewhere on the board

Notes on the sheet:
Reference Voltage Circuit
DC/DC Converter to 5V
Power Input
Bus Voltage Circuit

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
